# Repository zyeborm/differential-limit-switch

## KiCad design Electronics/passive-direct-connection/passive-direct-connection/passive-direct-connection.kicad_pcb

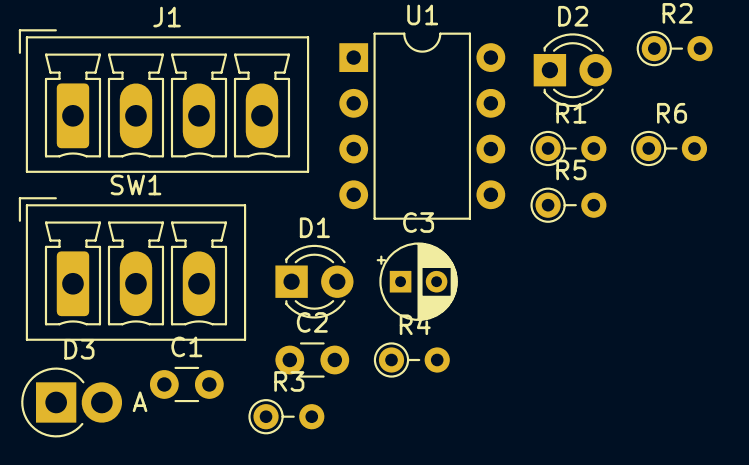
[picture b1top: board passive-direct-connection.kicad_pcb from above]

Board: 2 copper layers, 15 parts (0 on the bottom side), 10 nets, no tracks yet.

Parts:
C1, C2: .1uf; C_Disc_D3.0mm_W1.6mm_P2.50mm
C3: 10uf; CP_Radial_D4.0mm_P2.00mm
D1, D2: LED_Small; LED_D3.0mm_Clear
D3: 1N4004; D_DO-15_P2.54mm_Vertical_AnodeUp
J1: Conn_01x04_Male; PhoenixContact_MCV_1,5_4-G-3.5_1x04_P3.50mm_Vertical
R1, R5: 240; R_Axial_DIN0204_L3.6mm_D1.6mm_P2.54mm_Vertical
R2, R4, R6: 2.2k; R_Axial_DIN0204_L3.6mm_D1.6mm_P2.54mm_Vertical
R3: 2.2K; R_Axial_DIN0204_L3.6mm_D1.6mm_P2.54mm_Vertical
SW1: SW_SPDT; PhoenixContact_MCV_1,5_3-G-3.5_1x03_P3.50mm_Vertical
U1: SN75LBC176P; DIP-8_W7.62mm

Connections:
+5V: C2.1, C3.1, J1.4, R1.1, R3.2, R6.1, U1.8
GND: C1.1, C2.2, C3.2, J1.1, R2.2, SW1.2, U1.5
unnamed: C1.2, R4.2, R5.2, U1.4
unnamed: D1.1, R2.1
unnamed: D1.2, D2.1, D3.2, R1.2, R4.1, SW1.1
unnamed: D2.2, R3.1
unnamed: D3.1, R5.1
unnamed: J1.2, U1.6
unnamed: J1.3, U1.7
unnamed: R6.2, U1.2, U1.3

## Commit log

2020-08-06 Initial passive based Tx schematic
2020-08-07 added debounce and assigned components
2020-08-07 set connectors to vertical
